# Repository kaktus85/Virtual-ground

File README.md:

# Virtual Ground
This repository contains all the available documentation and source files for Virtual ground project.
- A copy of this is also available on Google Drive: https://drive.google.com/drive/folders/0B7G3xJXZNLUpb3VGYXRuN05VMTg
- An article about this project is here: kaktuscircuits.blogspot.com/2016/04/virtual-ground.html and on Hackaday.io: https://hackaday.io/project/11066-virtual-ground

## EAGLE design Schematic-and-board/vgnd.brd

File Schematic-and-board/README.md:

# Schematic and Board
- Cadsoft Eagle source files for the PCB of Virtual ground.
- A PNG schematic also included for a quick reference without having to install Eagle.
- Top and bottom PCB view from OSHPark.
- Don't forget to add 100nF capacitor directly on opamp's input pins 4 and 5!

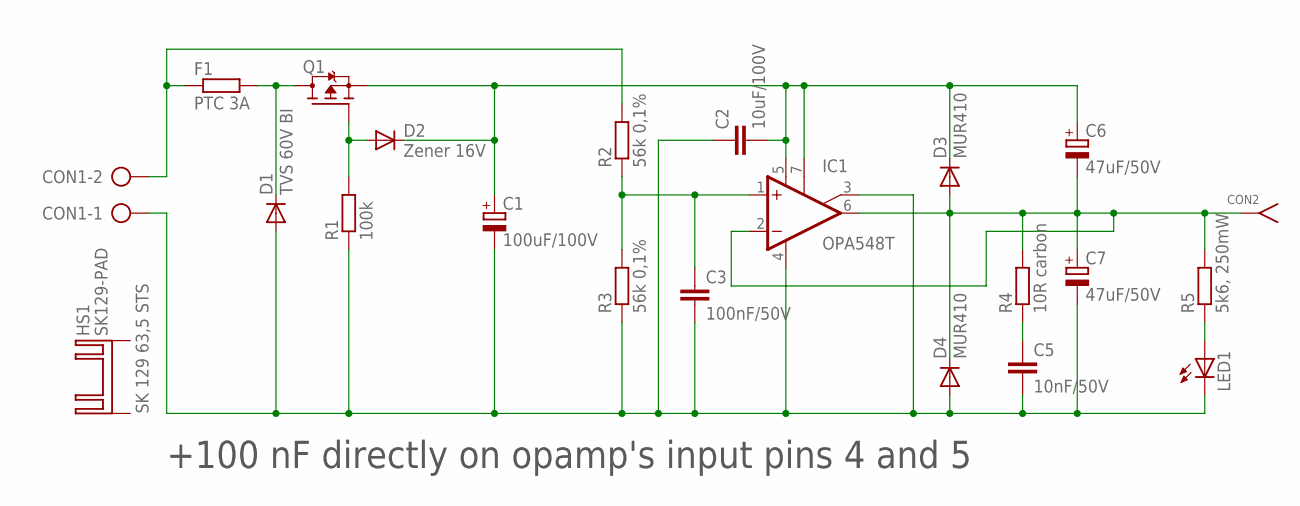
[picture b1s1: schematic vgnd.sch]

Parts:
C1: 100uF/100V; E5-10,5
C2: 10uF/100V; C2220K
C3: 100nF/50V; C0603
C5: 10nF/50V; C0603
C6, C7: 47uF/50V; E2,5-7
CON1: AK500/2
CON2: FCR7350; BANANA-PCB-S16N
D1: TVS 60V BI; SMC
D2: Zener 16V; SOD323-R
D3, D4: MUR410; DO201-15
F1: PTC 3A; 0309/10
HS1: SK129-PAD; SK129
IC1: OPA548T; TO220-7
LED1: LEDCHIPLED_0603; CHIPLED_0603
Q1: FDD4141TO252; TO252
R1: 100k; R0603
R2, R3: 56k 0,1%; R0603
R4: 10R carbon; 0207/10
R5: 5k6, 250mW; M1206

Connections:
GND: C6.-, C7.+, CON2.P$1, CON2.P$2, CON2.P$3, CON2.P$4, CON2.P$5, D3.A, D4.C, IC1.2 (-IN), IC1.6 (OUT), R4.2, R5.2
unnamed: D1.C, F1.2, Q1.3 (D)
unnamed: C3.1, IC1.1 (+IN), R2.1, R3.2
unnamed: D2.A, Q1.1 (G), R1.2
unnamed: LED1.A, R5.1
unnamed: C5.1, R4.1
unnamed: CON1.2, F1.1, R2.2
NEG: C1.-, C2.1, C3.2, C5.2, C7.-, CON1.1, D1.A, D4.A, IC1.3 (ILIM), IC1.4 (V-), LED1.C, R1.1, R3.1
POS: C1.+, C2.2, C6.+, D2.C, D3.C, IC1.5 (V+), IC1.7 (E/S), Q1.2 (S)

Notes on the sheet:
+100 nF directly on opamp's input pins 4 and 5

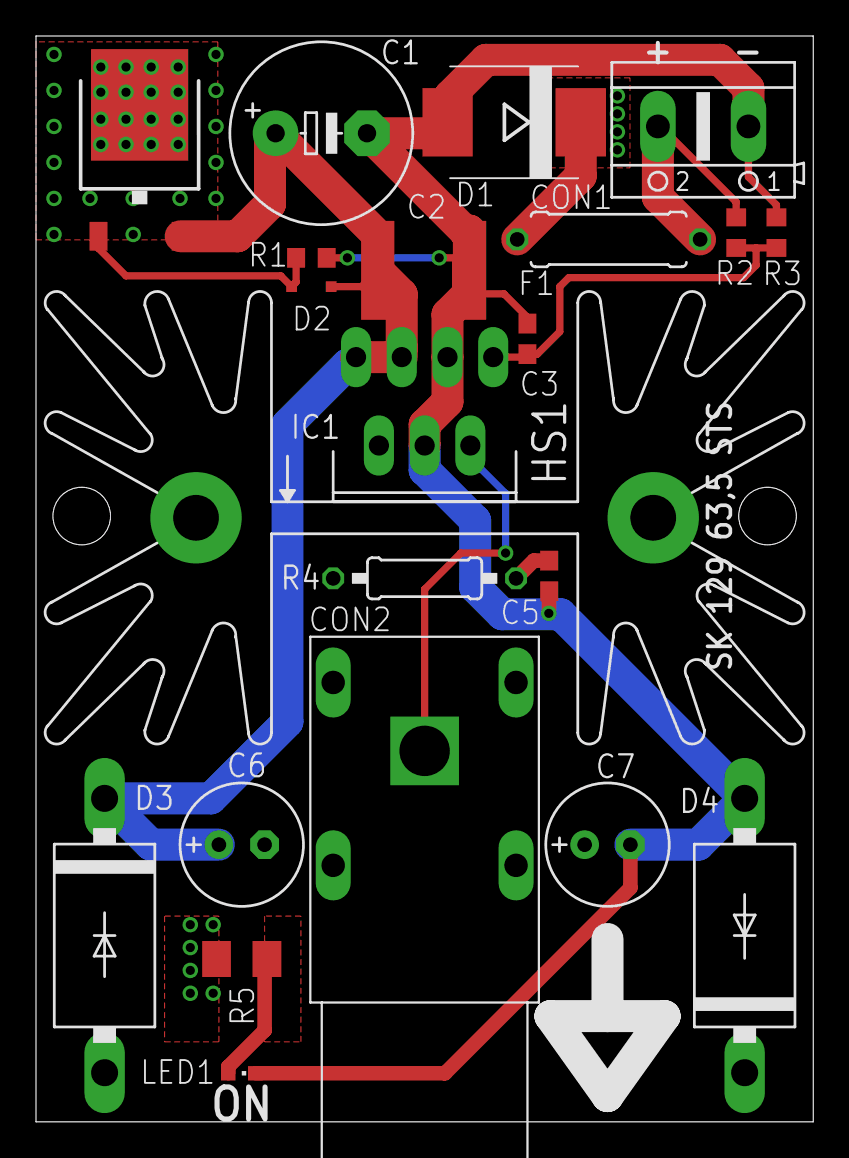
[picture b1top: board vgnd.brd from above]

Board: 2 copper layers, 43.2 x 60.3 mm, 22 parts (0 on the bottom side), 9 nets.

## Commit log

2016-07-01 :tada: Added .gitattributes & .gitignore files
2016-07-01 Initial files
2016-07-01 typo
